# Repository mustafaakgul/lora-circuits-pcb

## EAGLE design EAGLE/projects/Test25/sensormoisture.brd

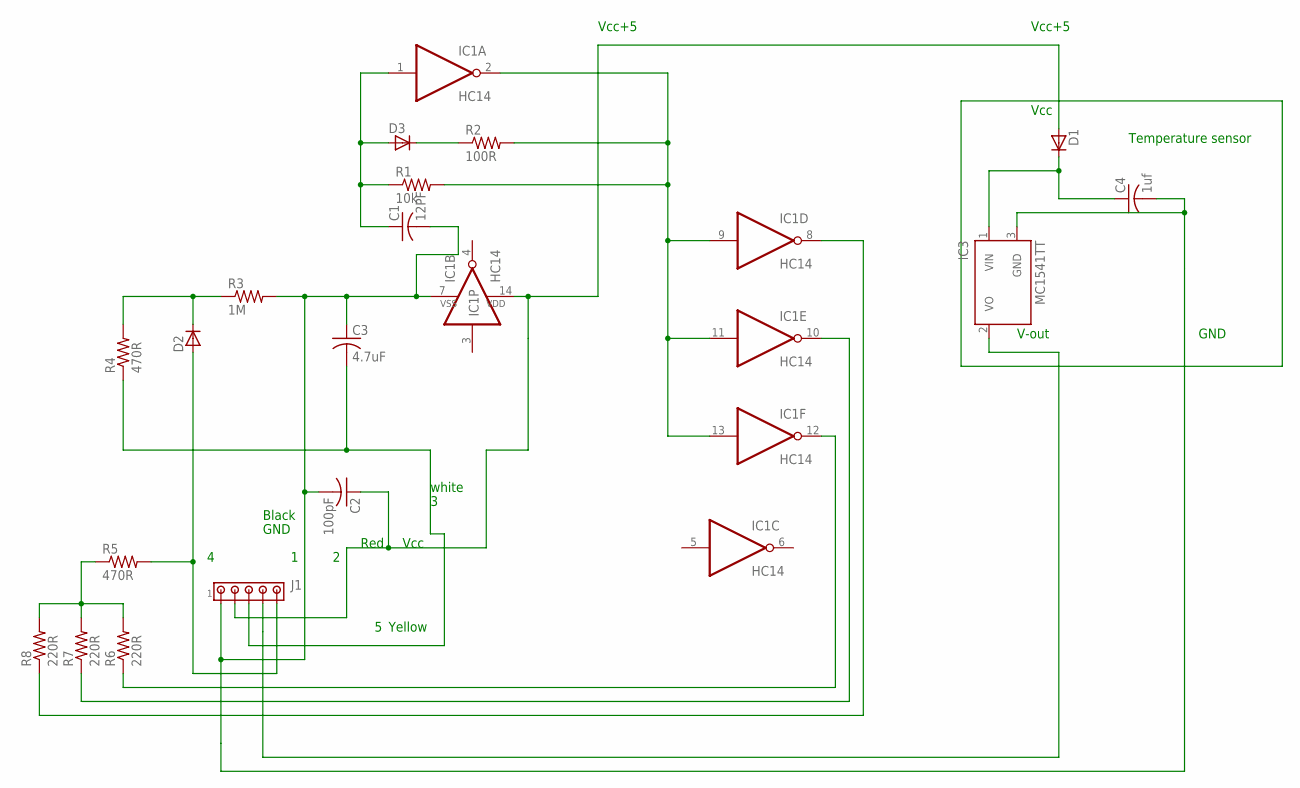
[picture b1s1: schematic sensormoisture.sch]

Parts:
C1: 12PF; C0805
C2: 100pF; C1206K
C3: 4.7uF; C1206
C4: 1uf; C1206K
D1, D2, D3: D-MLL-34; MELF-MLL34
IC1: HC14; SO14
IC3: MC1541TT; SOT23
J1: MTA05-100; 10X05MTA
R1: 10k; M0805
R2: 100R; M0805
R3: 1M; M0805
R4, R5: 470R; M0805
R6, R7, R8: 220R; M0805

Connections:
unnamed: C1.1, D3.2 (A), IC1.1 (I), R1.1
unnamed: D3.1 (C), R2.1
unnamed: IC1.2 (O), IC1.9 (I), IC1.11 (I), IC1.13 (I), R1.2, R2.2
unnamed: R5.1, R6.2, R7.2, R8.2
unnamed: C2.1, D1.2 (A), IC1.14 (VDD), J1.2
unnamed: C4.1, D1.1 (C), IC3.1 (VIN)
unnamed: D2.1 (C), R3.1, R4.2
unnamed: D2.2 (A), J1.5, R5.2
unnamed: C3.2, J1.3, R4.1
unnamed: IC1.12 (O), R6.1
unnamed: IC1.10 (O), R7.1
unnamed: IC1.8 (O), R8.1
unnamed: C1.2, C2.2, C3.1, C4.2, IC1.7 (VSS), IC3.3 (GND), J1.1, R3.2
unnamed: IC3.2 (VO), J1.4

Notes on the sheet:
Yellow
Vcc
GND
white
Red
Black
Vcc+5
Temperature sensor
V-out

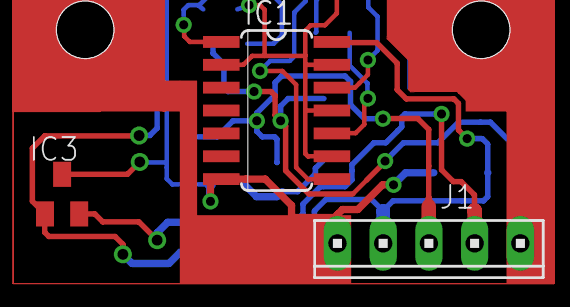
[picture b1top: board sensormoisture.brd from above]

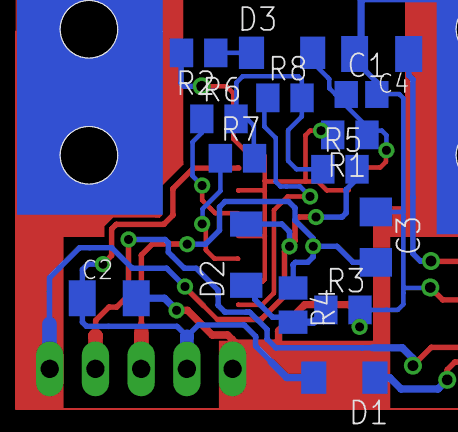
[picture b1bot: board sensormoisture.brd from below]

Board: 2 copper layers, 18 parts (15 on the bottom side), 14 nets.

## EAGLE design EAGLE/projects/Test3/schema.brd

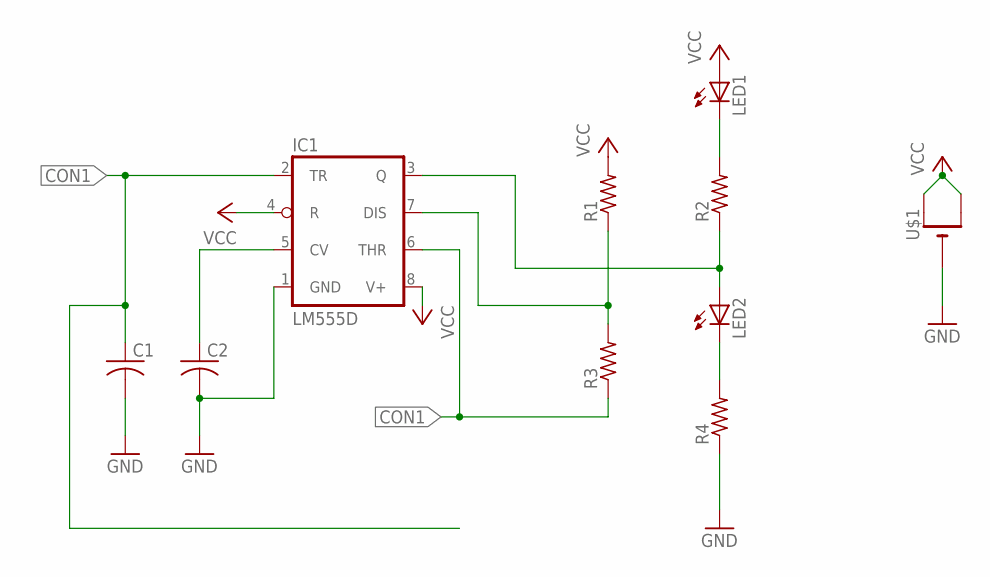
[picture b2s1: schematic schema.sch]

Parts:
C1, C2: C-USC0805; C0805
IC1: LM555D; SO08
LED1, LED2: LEDCHIPLED_0805; CHIPLED_0805
R1, R2, R3, R4: R-US_R0805; R0805
U$1: CR1220SMT; CR1220-SMD

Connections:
CON1: C1.1, IC1.2 (TR), IC1.6 (THR), R3.1
GND: C1.2, C2.2, IC1.1 (GND), R4.1, U$1.-
unnamed: C2.1, IC1.5 (CV)
unnamed: LED1.C, R2.2
unnamed: IC1.3 (Q), LED2.A, R2.1
unnamed: LED2.C, R4.2
unnamed: IC1.7 (DIS), R1.1, R3.2
VCC: IC1.4 (R), IC1.8 (V+), LED1.A, R1.2, U$1.+$1 (+), U$1.+$2 (+1)

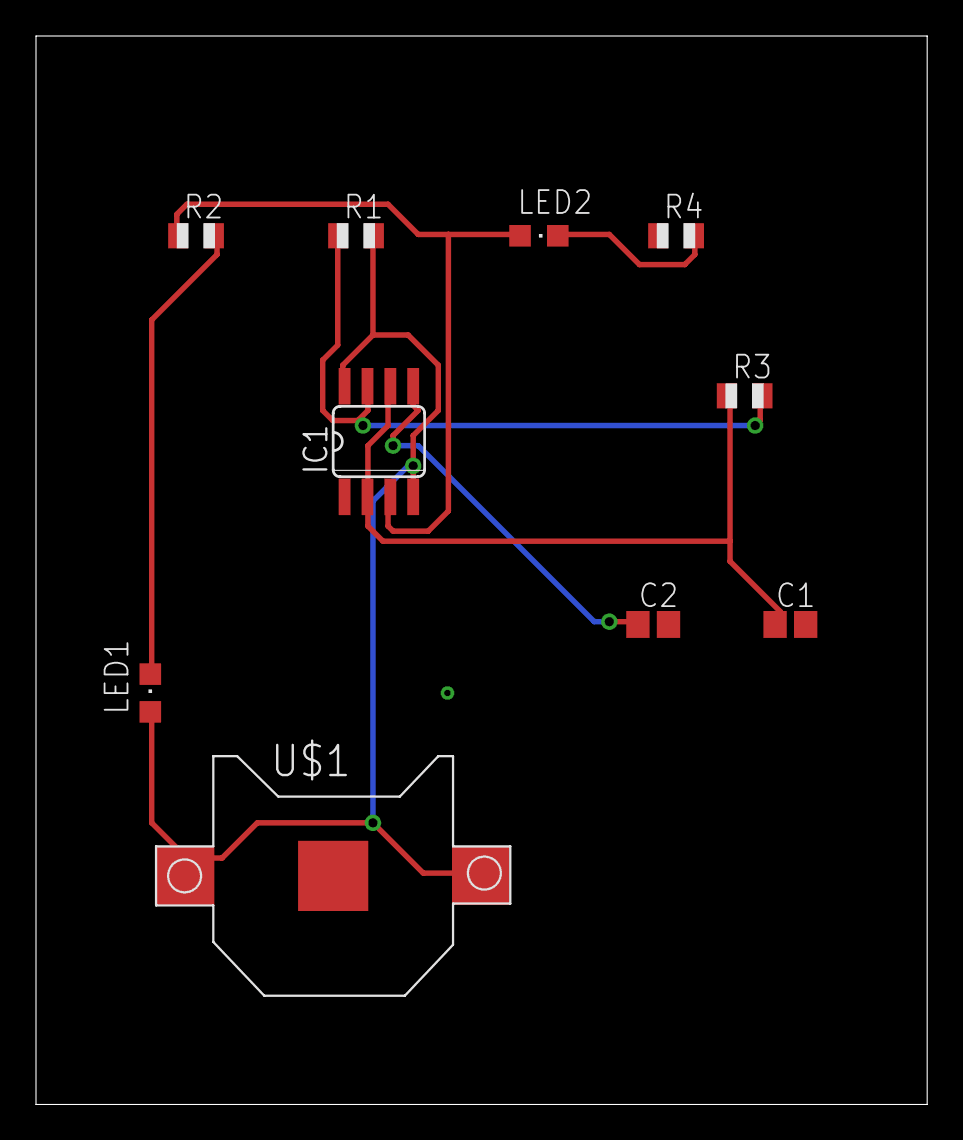
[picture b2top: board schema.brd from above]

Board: 2 copper layers, 49.5 x 59.4 mm, 10 parts (0 on the bottom side), 8 nets.

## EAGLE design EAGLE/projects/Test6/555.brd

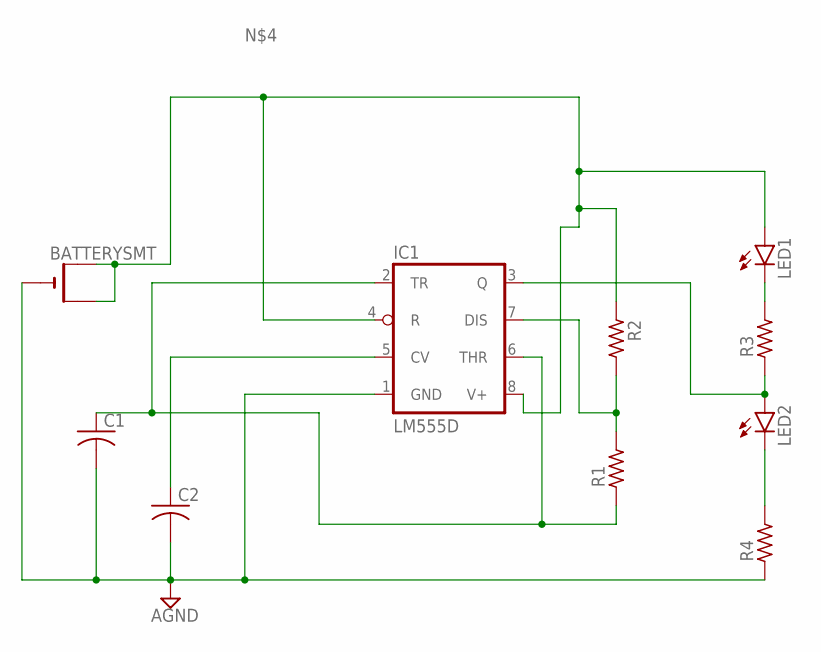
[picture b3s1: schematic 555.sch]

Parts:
BATTERYSMT: CR1220SMT; CR1220-SMD
C1, C2: C-USC0805; C0805
IC1: LM555D; SO08
LED1, LED2: LEDCHIP-LED0805; CHIP-LED0805
R1, R2, R3, R4: R_0805; R0805

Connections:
AGND: BATTERYSMT.-, C1.2, C2.2, IC1.1 (GND), R4.1
unnamed: C2.1, IC1.5 (CV)
unnamed: C1.1, IC1.2 (TR), IC1.6 (THR), R1.1
unnamed: IC1.7 (DIS), R1.2, R2.2
unnamed: BATTERYSMT.+$1 (+), BATTERYSMT.+$2 (+1), IC1.4 (R), IC1.8 (V+), LED1.A, R2.1
unnamed: IC1.3 (Q), LED2.A, R3.1
unnamed: LED1.C, R3.2
unnamed: LED2.C, R4.2

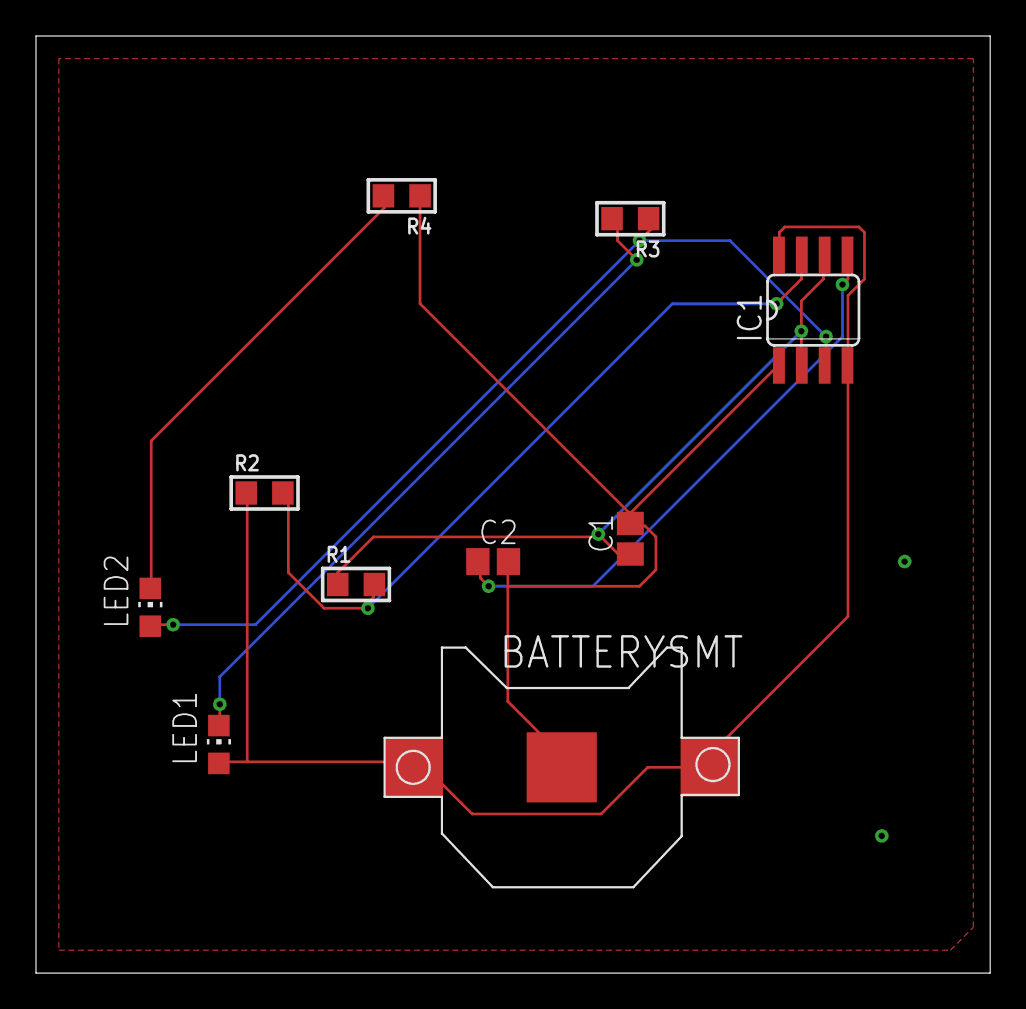
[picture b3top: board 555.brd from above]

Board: 2 copper layers, 53.0 x 52.1 mm, 10 parts (0 on the bottom side), 8 nets.

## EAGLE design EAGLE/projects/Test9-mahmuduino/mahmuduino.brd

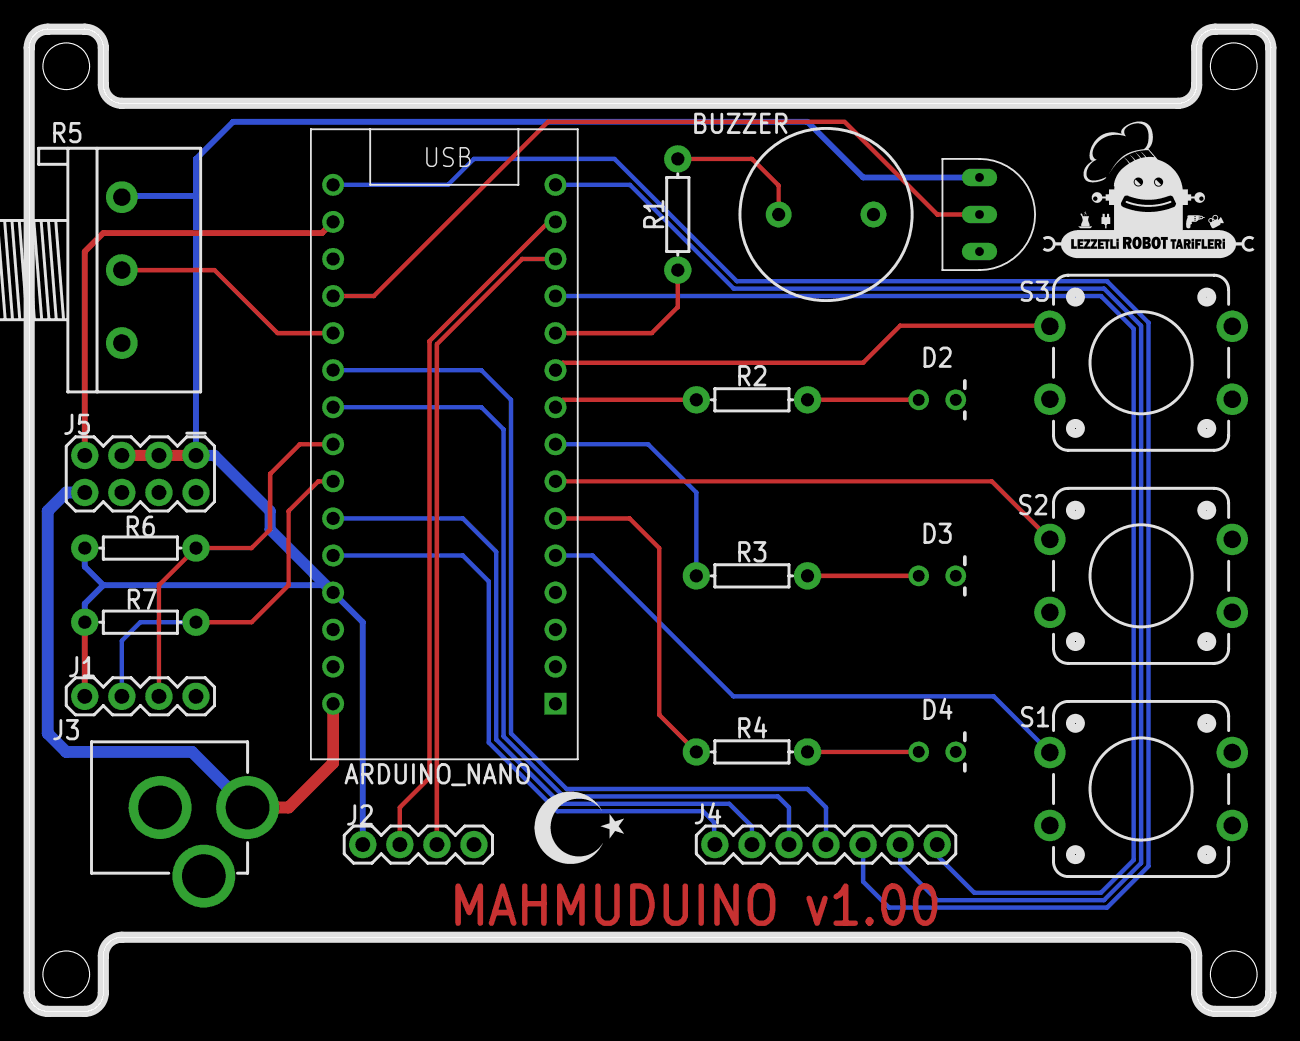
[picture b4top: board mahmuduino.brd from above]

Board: 2 copper layers, 85.1 x 67.3 mm, 24 parts (1 on the bottom side), 28 nets.

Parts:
ARDUINO_NANO: ARDUINO_NANO
BUZZER: BUZZER-PTH; BUZZER-12MM
D2, D3, D4: LED_3MM-NS
J1, J2: 1X04
J3: POWER; POWER_JACK_PTH
J4: 1X07
J5: 2X4
R1, R2, R3, R4: 330; AXIAL-0.3
R5: 3RP/1610N
R6, R7: 4700; AXIAL-0.3
S1, S2, S3: 12MM; TACTILE_SWITCH_PTH_12MM
U$1: LM35; TO-92
U$2, U$3: LRT-LOGO-0,0125-B
U$9: TR_MINI

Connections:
3.3V: ARDUINO_NANO.3V3, J5.7
A2: ARDUINO_NANO.A2, J4.4
A3: ARDUINO_NANO.A3, J4.5
A6: ARDUINO_NANO.A6, J4.6
A7: ARDUINO_NANO.A7, J4.7
BUTON1: ARDUINO_NANO.D2, S1.1
BUTON2: ARDUINO_NANO.D4, S2.1
BUTON3: ARDUINO_NANO.D7, S3.1
BUZZER: ARDUINO_NANO.D8, R1.P$1
D9: ARDUINO_NANO.D9, J4.1
D10_RX: ARDUINO_NANO.D10, J2.3
D11_TX: ARDUINO_NANO.D11, J2.2
D12: ARDUINO_NANO.D12, J4.2
D13: ARDUINO_NANO.D13, J4.3
GND: ARDUINO_NANO.GND@1, ARDUINO_NANO.GND@2, BUZZER.-, D2.K, D3.K, D4.K, J1.4, J2.4, J3.GND, J3.GNDBREAK, J5.2, J5.4, J5.6, R5.3, S1.3, S2.3, S3.3, U$1.3
LED1: ARDUINO_NANO.D3, R4.P$1
LED2: ARDUINO_NANO.D5, R3.P$1
LED3: ARDUINO_NANO.D6, R2.P$1
unnamed: BUZZER.+, R1.P$2
unnamed: D2.A, R2.P$2
unnamed: D3.A, R3.P$2
unnamed: D4.A, R4.P$2
SCL: ARDUINO_NANO.A5, J1.2, R7.P$1
SDA: ARDUINO_NANO.A4, J1.3, R6.P$1
VCC: ARDUINO_NANO.5V, J1.1, J2.1, J5.1, J5.3, J5.5, R5.1, R6.P$2, R7.P$2, U$1.1
VIN: ARDUINO_NANO.VIN, J3.PWR, J5.8
VOUT: ARDUINO_NANO.A0, U$1.2
VPOT: ARDUINO_NANO.A1, R5.2

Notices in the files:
parts and their libraries:
SparkFun: Licensing: CC v3.0 Share-Alike You are welcome to use this library for commercial purposes.
cap_master-smd: Copyright (C) 2007, Bob Starr
SparkFun-LED: Licensing: Creative Commons ShareAlike 4.0 International - https://creativecommons.org/licenses/by-sa/4.0
